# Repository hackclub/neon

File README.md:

uhh for backend to build for rust, just set RUN_LANGUAGE=rust as an env variable, and the same for go.

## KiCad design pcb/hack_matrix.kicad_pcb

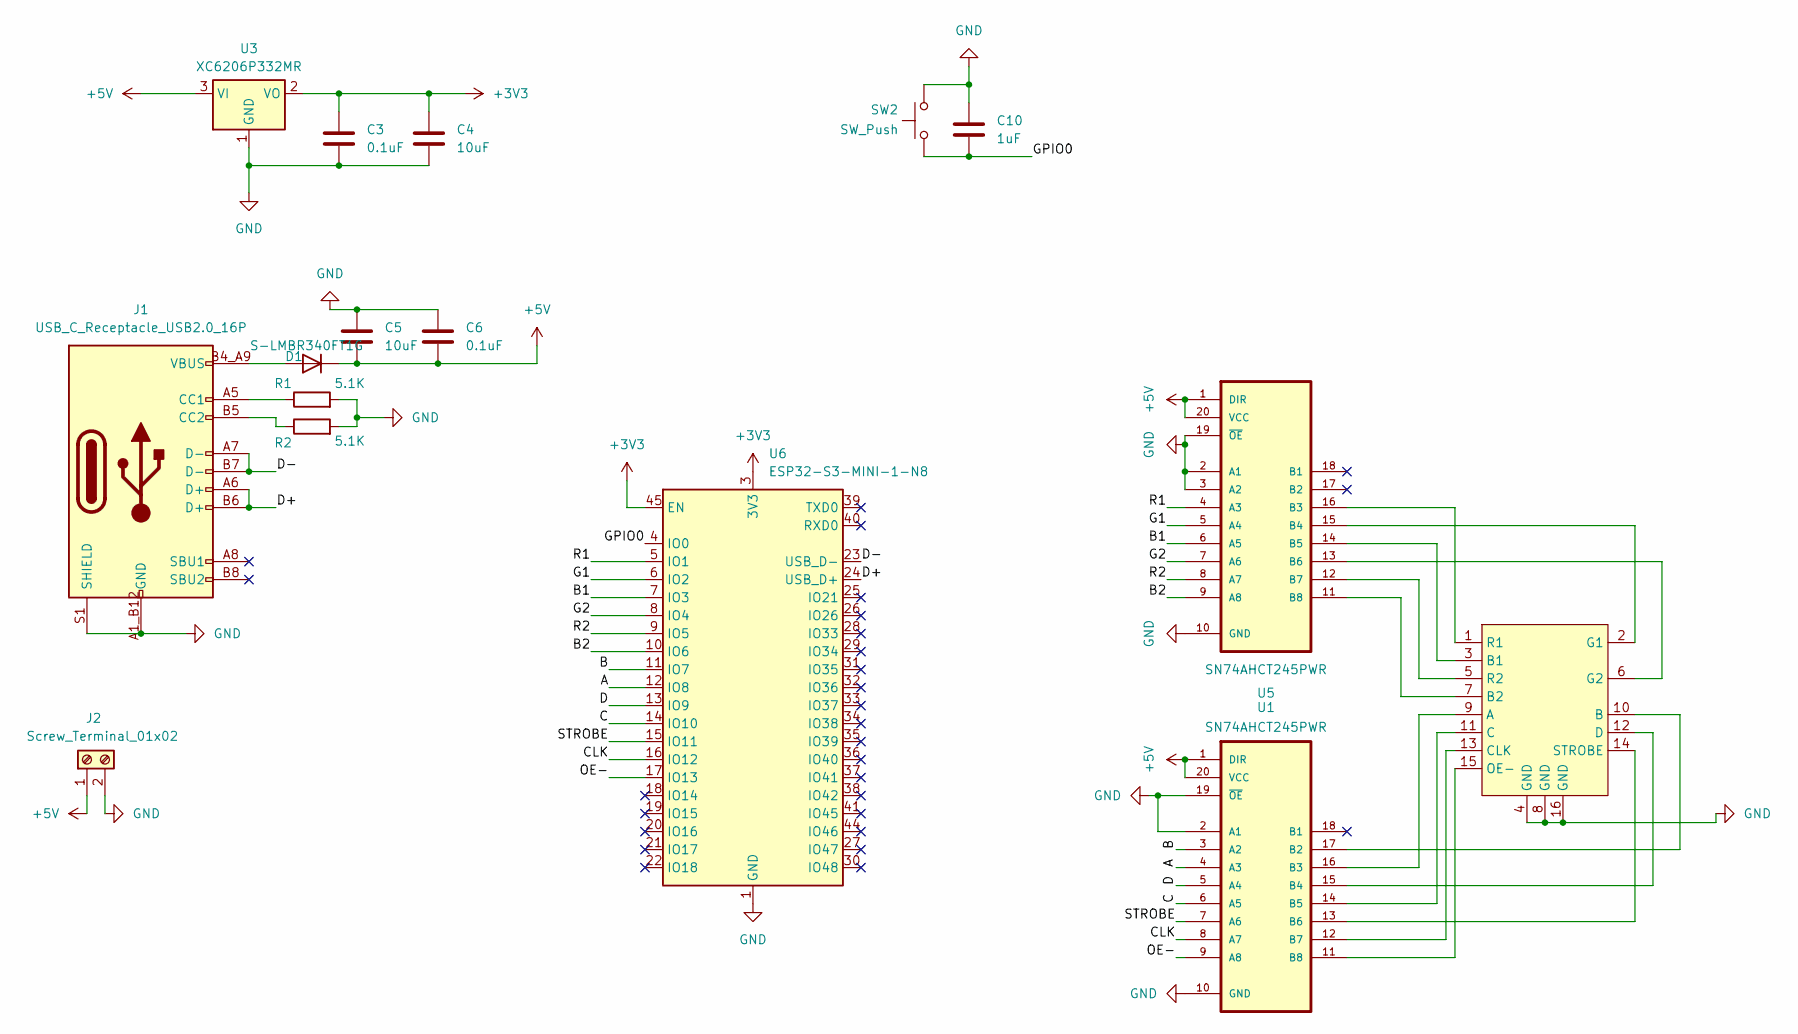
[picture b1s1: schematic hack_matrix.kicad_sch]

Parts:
C3, C6: 0.1uF; C_0402_1005Metric; LCSC C106209
C4, C5: 10uF; C_0402_1005Metric; LCSC C15525
C10: 1uF; C_0402_1005Metric; LCSC C14445
D1: S-LMBR340FT1G; D_SOD-123F; LCSC C2972823
J1: USB_C_Receptacle_USB2.0_16P; HRO_TYPE-C-31-M-12; LCSC C165948
J2: Screw_Terminal_01x02; DB300V-5.0-2P-BU-S; LCSC C881705
R1, R2: 5.1K; R_0402_1005Metric; LCSC C25905
SW2: SW_Push; SW_TS-1088-AR02016; LCSC C720477
U1, U5: SN74AHCT245PWR; SOP65P640X120-20N; LCSC C6779
U2: PinSocket_2x08_P2.54mm_Vertical; LCSC C30734
U3: XC6206P332MR; SOT-23; LCSC C347376
U6: ESP32-S3-MINI-1-N8; ESP32-S2-MINI-1; LCSC C2913206

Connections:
+3V3: C3.1, C4.1, U3.2 (VO), U6.3 (3V3), U6.45 (EN)
+5V: C5.2, C6.2, D1.1 (K), J2.1, U1.1 (DIR), U1.20 (VCC), U3.3 (VI), U5.1 (DIR), U5.20 (VCC)
/A: U1.4 (A3), U6.12 (IO8)
/B: U1.3 (A2), U6.11 (IO7)
/B1: U5.6 (A5), U6.7 (IO3)
/B2: U5.9 (A8), U6.10 (IO6)
/C: U1.6 (A5), U6.14 (IO10)
/CLK: U1.8 (A7), U6.16 (IO12)
/D: U1.5 (A4), U6.13 (IO9)
/D+: J1.A6 (D+), J1.B6 (D+), U6.24 (USB_D+)
/D-: J1.A7 (D-), J1.B7 (D-), U6.23 (USB_D-)
/G1: U5.5 (A4), U6.6 (IO2)
/G2: U5.7 (A6), U6.8 (IO4)
/GPIO0: C10.2, SW2.1, U6.4 (IO0)
/OE-: U1.9 (A8), U6.17 (IO13)
/R1: U5.4 (A3), U6.5 (IO1)
/R2: U5.8 (A7), U6.9 (IO5)
/STROBE: U1.7 (A6), U6.15 (IO11)
GND: C3.2, C4.2, C5.1, C6.1, C10.1, J1.A1_B12 (GND), J1.B1_A12 (GND), J1.S1 (SHIELD), J1.S2 (SHIELD), J1.S3 (SHIELD), J1.S4 (SHIELD), J2.2, R1.2, R2.2, SW2.2, U1.2 (A1), U1.10 (GND), U1.19 (~OE), U2.4 (GND), U2.8 (GND), U2.16 (GND), U3.1 (GND), U5.2 (A1), U5.3 (A2), U5.10 (GND), U5.19 (~OE), U6.1 (GND), U6.2 (GND), U6.42 (GND), U6.43 (GND), U6.46 (GND), U6.47 (GND), U6.48 (GND), U6.49 (GND), U6.50 (GND), U6.51 (GND), U6.52 (GND), U6.53 (GND), U6.54 (GND), U6.55 (GND), U6.56 (GND), U6.57 (GND), U6.58 (GND), U6.59 (GND), U6.60 (GND), U6.61 (GND), U6.62 (GND), U6.63 (GND), U6.64 (GND), U6.65 (GND)
unnamed: D1.2 (A), J1.A4_B9 (VBUS), J1.B4_A9 (VBUS)
unnamed: J1.A5 (CC1), R1.1
unnamed: J1.B5 (CC2), R2.1
unnamed: U1.17 (B2), U2.10 (B)
unnamed: U1.16 (B3), U2.9 (A)
unnamed: U1.15 (B4), U2.12 (D)
unnamed: U1.14 (B5), U2.11 (C)
unnamed: U1.13 (B6), U2.14 (STROBE)
unnamed: U1.12 (B7), U2.13 (CLK)
unnamed: U1.11 (B8), U2.15 (OE-)
unnamed: U2.3 (B1), U5.14 (B5)
unnamed: U2.7 (B2), U5.11 (B8)
unnamed: U2.2 (G1), U5.15 (B4)
unnamed: U2.6 (G2), U5.13 (B6)
unnamed: U2.1 (R1), U5.16 (B3)
unnamed: U2.5 (R2), U5.12 (B7)

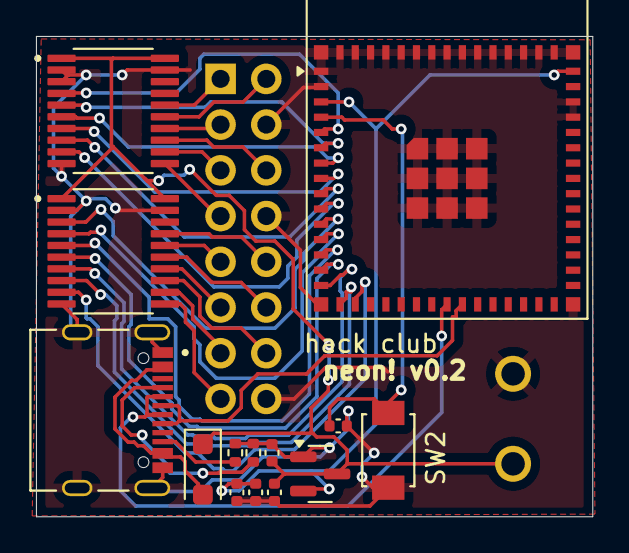
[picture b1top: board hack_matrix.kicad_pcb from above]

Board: 11 copper layers, 30.9 x 26.7 mm, 16 parts (1 on the bottom side), 35 nets.

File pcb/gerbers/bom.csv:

"Reference","Value","LCSC","Datasheet","Footprint","Qty","DNP"
"U1,U5","SN74AHCT245PWR","C6779","","SOP65P640X120-20N:SOP65P640X120-20N","2",""
"U6","ESP32-S3-MINI-1-N8","C2913206","https://www.espressif.com/sites/default/files/documentation/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","RF_Module:ESP32-S2-MINI-1","1",""
"U3","XC6206P332MR","C347376","http://www.advanced-monolithic.com/pdf/ds1117.pdf","Package_TO_SOT_SMD:SOT-23","1",""
"U2","~","C30734","","Connector_PinSocket_2.54mm:PinSocket_2x08_P2.54mm_Vertical","1",""
"SW2","SW_Push","C720477 ","~","TS-1088-AR02016:SW_TS-1088-AR02016","1",""
"R1,R2","5.1K","C25905","~","Resistor_SMD:R_0402_1005Metric","2",""
"J2","Screw_Terminal_01x02","C881705","~","DORABO:DB300V-5.0-2P-BU-S","1",""
"J1","USB_C_Receptacle_USB2.0_16P","C165948","https://www.usb.org/sites/default/files/documents/usb_type-c.zip","HRO_TYPE-C-31-M-12:HRO_TYPE-C-31-M-12","1",""
"D1","S-LMBR340FT1G","C2972823","~","Diode_SMD:D_SOD-123F","1",""
"C10","1uF","C14445","~","Capacitor_SMD:C_0402_1005Metric","1",""
"C4,C5","10uF","C15525","~","Capacitor_SMD:C_0402_1005Metric","2",""
"C3,C6","0.1uF","C106209","~","Capacitor_SMD:C_0402_1005Metric","2",""

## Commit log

2025-01-03 update to fix USB wiring / EN pin.
    TODO: fix screw jack part #
2025-01-08 move pcb into its own dir
2025-01-13 init backend
2025-01-13 get some things working? shared memory is wacky. lots of broken code
2025-01-15 prototype semi-working-ish
2025-01-15 add frontend (almost works?)
2025-01-15 codemirror working
2025-01-16 dockerize simulation workers / allow multiple users!
2025-01-16 stream console messages
2025-01-16 basically drop-in
2025-01-16 save to localstorage
2025-01-16 replace default example
2025-01-17 dockerize all the kingdoms
2025-01-17 make work w/ coolify?
2025-01-17 hello world
2025-01-17 coolify backend domain
2025-01-17 gridlines + correct colors
2025-01-17 scuffed css
2025-01-17 quick fixes; make running state work
2025-01-17 remove unnecesary files
2025-01-21 website progress
2025-01-22 move font import to Layout.astro
2025-01-22 above the fold is hard
2025-01-22 better above-the-fold
2025-01-22 initial faq
2025-01-22 more faq
2025-01-22 #neon-ysws -> #neon
2025-01-23 monospace font
2025-01-23 change title
2025-01-23 fix website end date
2025-01-23 add requests
2025-01-23 title: Neons -> Neon
2025-01-23 esp32-s2 -> esp32-s3
2025-01-23 whoopsies add a license
2025-01-23 add mqtt
2025-01-23 forgor an equals sign
2025-01-24 add hashlib
2025-01-26 support for files!
2025-01-26 fix query params seperator in websocket init
2025-01-27 probably inefficient code, but its fast af so ship it wooo
2025-01-27 make a singular docker thing to build both with a flag to choose which one
2025-01-27 ok fixed it, (it got uh broken (i 100% wasnt being tired n messed it up))
2025-01-27 dind + resource limits :)
2025-01-29 open github repos!
2025-01-29 add warning for /open
2025-01-29 add vercel adapter
2025-01-31 up resource limits
2025-02-01 make overflow-x scroll for console output!
2025-02-01 temporarily up resource limits for huddle! gotta lock in
2025-02-01 add circuitpython-display-shapes
2025-02-01 change the logo to not the default one
2025-02-03 add adafruit-circuitpython-imageload
2025-02-04 gallery (in-progress) + 404 if /open link is bad
2025-02-04 fix fonts not loading?
2025-02-04 ok astro doesn't want to work?? fixing font again
2025-02-04 add author name/link
2025-02-04 hacky gitlab link parsing
2025-02-04 gallery side margins + subtitle
2025-02-25 Fixes live code link for many neon submissions, many used neon.py
